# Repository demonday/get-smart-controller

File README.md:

# Modern Replacement for "GET" Smart Wireless Lighting System Controller

## Project Intro
I have a aging Wireless Lighting System from a UK company called GET, from circa 2007. Its now so old in fact, that its no longer manufatured, and the company is no longer in existance.
The setup includes a battery-operated controller (replacing the traditional UK light switch) and some mains supplied receivers to operate the lights. I buried the recievers behind the plasterboard in my apartment's ceiling when I installed the system.
Its operated flawlessly since then, I don't think I've ever changed the batteries in the controller, which is testament to its solid design.

It is however, missing integration with home automation (I use Home Assistant & Alexa). Its now a deal breaker. I could replace them with somethine else, and repair the plaster.... 
... but rather than add to the e-waste pile, I thought I'd put one of those microcontroller's I have in a box to good use.

## Side Quests
Typically for me, I'm also diving into a few related technologies as part of this project:
- **Zephyr**: I'm curious to learn this framework.
- **Home Assistant Integration**: I use HA for all my other stuff so this is given.
- **Thread/Matter**: I have tons Zigbee devices already, and want learn more about the newer connected device protocols.

Built with Zephyr v3.6.0

# Reverse Engineering the Controller
After some snooping inside the contoller it seems to be 433Mhz FSK, based on a HiMark TX4915-LF RF chip. Only datasheets HiMark TX4915 say its for ASK, but the silksreen on the transmiter clearly says 433 FSK.

## My Controller Setup
From the [GET Smart Wireless Lighting System Manual](https://www.tlc-direct.co.uk/Technical/DataSheets/GET/Smart_user.pdf) I'm using the controller in "Dimming Mode", with 2 lights, on buttons 1 and 2 respectively.

## Sniffing the data
Before I opened the controller 
Bring on the Hack RF One. 

# Upgrading the GET - Smart Wireless Lighting System Controller

## Reach Out
For collaboration or feedback, please feel free to contact me at [ngormley at armadillo.ie]

*Thank you for your interest*

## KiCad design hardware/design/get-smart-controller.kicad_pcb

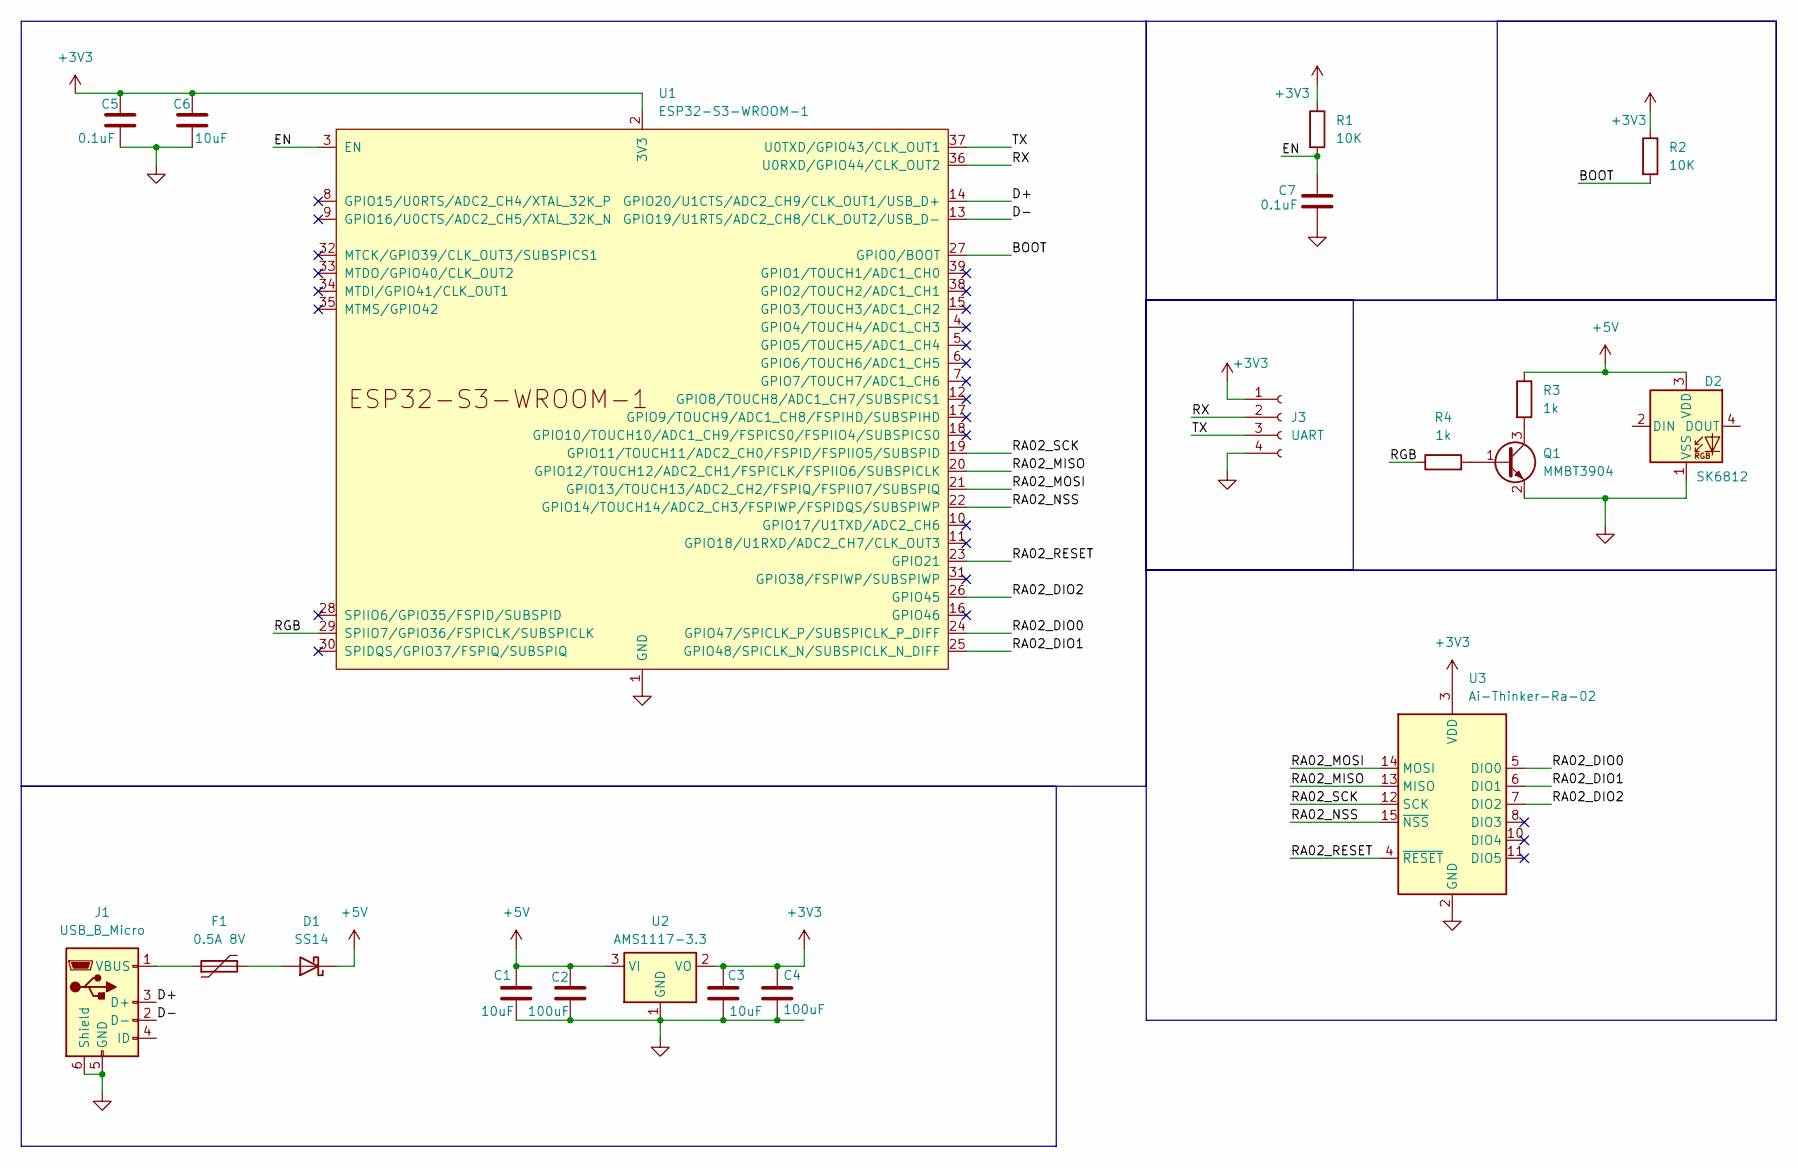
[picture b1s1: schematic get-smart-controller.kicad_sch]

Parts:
C1, C3, C6: 10uF; C_0805_2012Metric_Pad1.18x1.45mm_HandSolder
C2, C4: 100uF; C_1206_3216Metric_Pad1.33x1.80mm_HandSolder
C5, C7: 0.1uF; C_0805_2012Metric_Pad1.18x1.45mm_HandSolder
D1: SS14; D_SOD-323_HandSoldering
D2: SK6812; LED_SK6812_PLCC4_5.0x5.0mm_P3.2mm
F1: 0.5A 8V; Fuse_1206_3216Metric_Pad1.42x1.75mm_HandSolder
J1: USB_B_Micro; USB_Micro-B_Custom
J3: UART; JST_PH_S4B-PH-K_1x04_P2.00mm_Horizontal
Q1: MMBT3904; SOT-23
R1, R2: 10K; R_0805_2012Metric_Pad1.20x1.40mm_HandSolder
R3, R4: 1k; R_0805_2012Metric_Pad1.20x1.40mm_HandSolder
U1: ESP32-S3-WROOM-1
U2: AMS1117-3.3; SOT-223-3_TabPin2
U3: Ai-Thinker-Ra-02; Ai-Thinker-Ra-01-LoRa

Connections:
+3V3: C3.1, C4.1, C5.1, C6.1, J3.1, R1.1, R2.1, U1.2 (3V3), U2.2 (VO), U3.3 (VDD)
+5V: C1.1, C2.1, D1.1 (K), D2.3 (VDD), R3.1, U2.3 (VI)
/BOOT: R2.2, U1.27 (GPIO0/BOOT)
/D+: J1.3 (D+), U1.14 (GPIO20/U1CTS/ADC2_CH9/CLK_OUT1/USB_D+)
/D-: J1.2 (D-), U1.13 (GPIO19/U1RTS/ADC2_CH8/CLK_OUT2/USB_D-)
/EN: C7.1, R1.2, U1.3 (EN)
/RA02_DIO0: U1.24 (GPIO47/SPICLK_P/SUBSPICLK_P_DIFF), U3.5 (DIO0)
/RA02_DIO1: U1.25 (GPIO48/SPICLK_N/SUBSPICLK_N_DIFF), U3.6 (DIO1)
/RA02_DIO2: U1.26 (GPIO45), U3.7 (DIO2)
/RA02_MISO: U1.20 (GPIO12/TOUCH12/ADC2_CH1/FSPICLK/FSPIIO6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), U3.13 (MISO)
/RA02_MOSI: U1.21 (GPIO13/TOUCH13/ADC2_CH2/FSPIQ/FSPIIO7/S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), U3.14 (MOSI)
/RA02_NSS: U1.22 (GPIO14/TOUCH14/ADC2_CH3/FSPIWP/FSPIDQS/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), U3.15 (~NSS)
/RA02_RESET: U1.23 (GPIO21), U3.4 (~RESET)
/RA02_SCK: U1.19 (GPIO11/TOUCH11/ADC2_CH0/FSPID/FSPIIO5/S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), U3.12 (SCK)
/RGB: R4.1, U1.29 (SPIIO7/GPIO36/FSPICLK/SUBSPICLK)
/RX: J3.2, U1.36 (U0RXD/GPIO44/CLK_OUT2)
/TX: J3.3, U1.37 (U0TXD/GPIO43/CLK_OUT1)
GND: C1.2, C2.2, C3.2, C4.2, C5.2, C6.2, C7.2, D2.1 (VSS), J1.5 (GND), J1.6 (Shield), J3.4, Q1.2 (E), U1.1 (GND), U1.40 (GND), U1.41 (GND), U2.1 (GND), U3.1 (GND), U3.2 (GND), U3.9 (GND), U3.16 (GND)
unnamed: D1.2 (A), F1.2
unnamed: F1.1, J1.1 (VBUS)
unnamed: Q1.1 (B), R4.2
unnamed: Q1.3 (C), R3.2

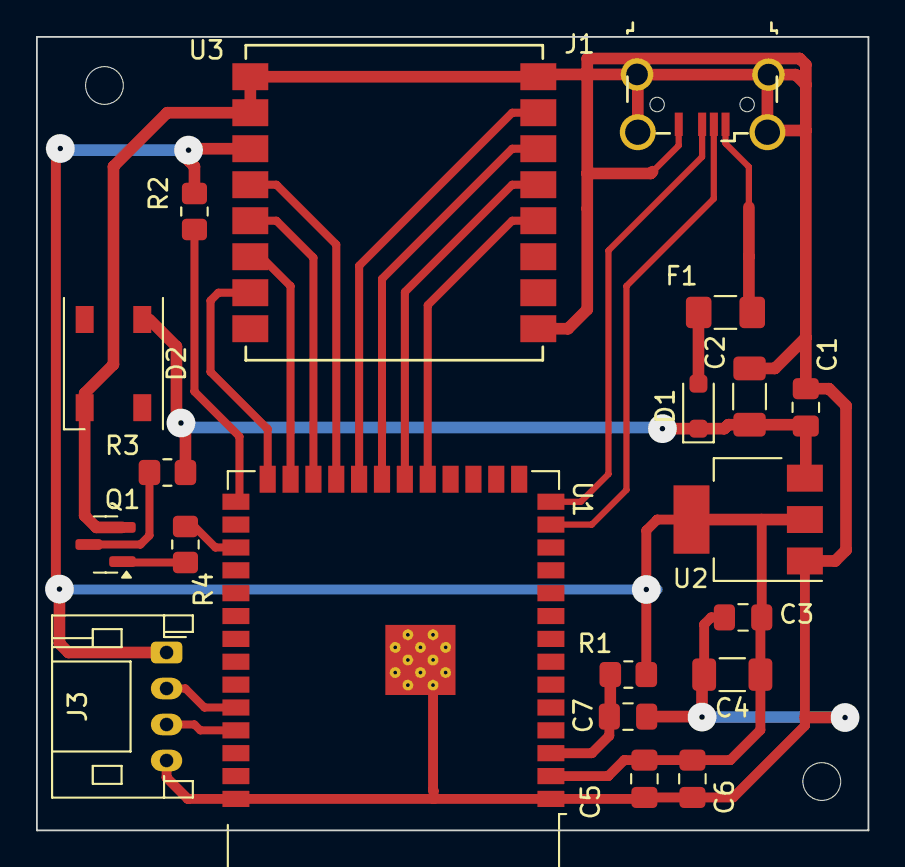
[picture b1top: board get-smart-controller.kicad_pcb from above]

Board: 2 copper layers, 46.2 x 44.1 mm, 22 parts (0 on the bottom side), 22 nets.

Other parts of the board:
H1, H3: MountingHole_2.1mm

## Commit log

2023-12-18 Zephyr .gitignore
2023-12-18 First pass at controller for GET - Smart Wireless Lighting System
2023-12-18 Using FIFO hangs when trying to publish message. Moving to ZBUS
2023-12-19 MQTT and controller all working. Now for the radio...
2024-01-01 change mqtt server
2024-01-02 integrate radiolib and refactor for esp32s3
2024-01-03 working prototype supports on/off and dim.
2024-01-03 Create README.md
    First pass a the README
2024-02-05 Added Espressif KiCad resources
2024-02-06 Added KiCad exclusions
2024-02-06 Added Homebrew PCB in KiCad
2024-02-08 Updated PCB with holes
2024-03-12 Add additional Ground path
2024-03-12 fixed issues with getting the byte sequences
2024-03-16 Added RGB led, and fixed foorptint for USB Micro
2026-01-08 Add watchdog timer and improve system stability
    - Implement 10-second watchdog timer with 1-second feed interval
    - Fix WiFi connectivity and MQTT authentication issues
    - Configure USB serial console for ESP32-S3
    - Improve memory management and thread safety
    - Add runtime statistics for heap and thread monitoring
    - Fix device ID storage and configuration management
